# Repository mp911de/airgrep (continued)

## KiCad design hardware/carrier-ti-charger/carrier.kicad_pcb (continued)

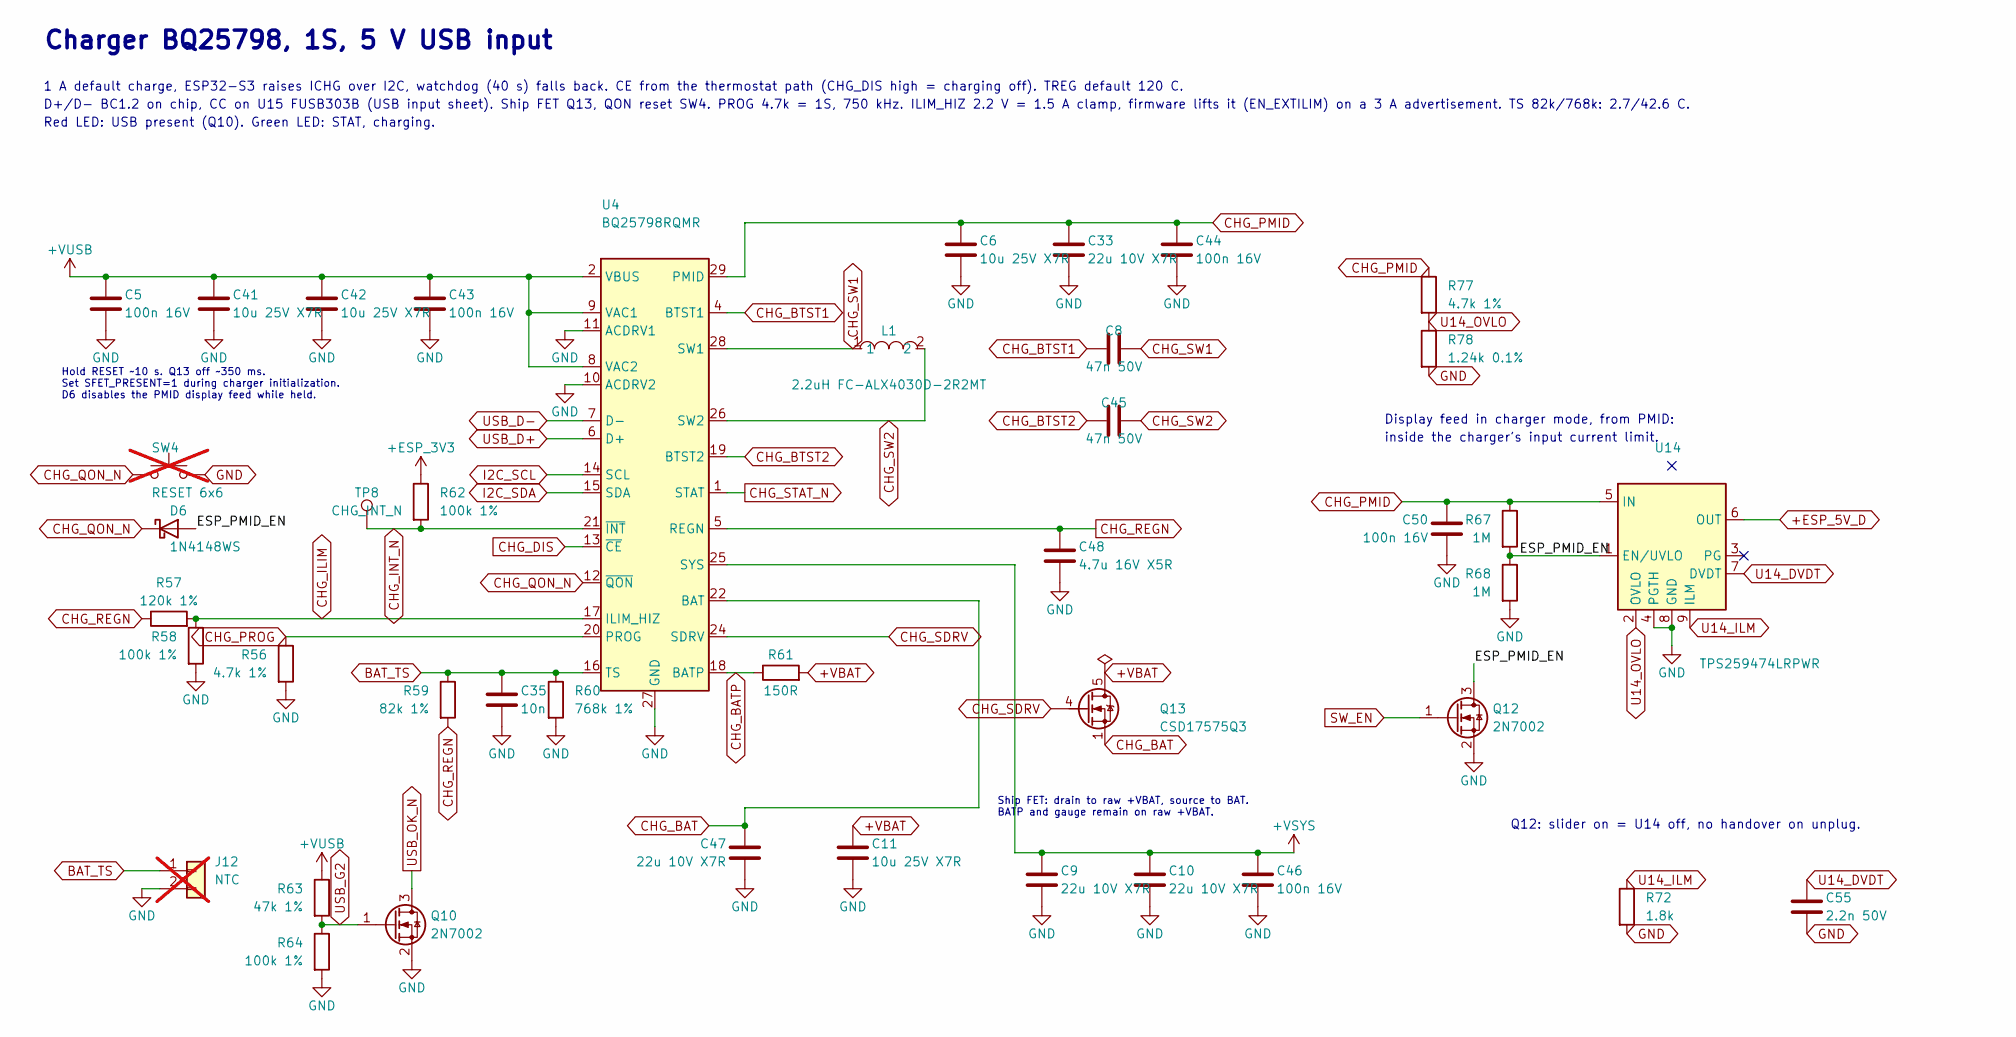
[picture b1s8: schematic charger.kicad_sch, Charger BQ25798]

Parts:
C5, C43, C44, C46, C50: 100n 16V; C_0402_1005Metric_NoSilk; MPN CL05B104KO5NNNC; LCSC C1525
C6, C11, C41, C42: 10u 25V X7R; C_0805_2012Metric; LCSC C3039694
C8, C45: 47n 50V; C_0603_1608Metric; LCSC C1622
C9, C10, C33, C47: 22u 10V X7R; C_0805_2012Metric; LCSC C907991
C35: 10n; C_0603_1608Metric; LCSC C57112
C48: 4.7u 16V X5R; C_0603_1608Metric; LCSC C19666
C55: 2.2n 50V; C_0603_1608Metric; MPN 0603B222K500NT; LCSC C1604
D6: 1N4148WS; D_SOD-323; MPN 1N4148WS; LCSC C2128
J12: NTC; JST_PH_B2B-PH-K_1x02_P2.00mm_Vertical_R10; not fitted
L1: 2.2uH FC-ALX4030D-2R2MT; IND-SMD_L4.2-W4.2_FC-ALX4030D; LCSC C5370906
Q10, Q12: 2N7002; SOT-23; LCSC C8545
Q13: CSD17575Q3; VSON-8_3.3x3.3mm_CSD17575Q3; LCSC C529277
R56: 4.7k 1%; R_0402_1005Metric_NoSilk; MPN 0402WGF4701TCE; LCSC C25900
R57: 120k 1%; R_0603_1608Metric; LCSC C25808
R58, R62, R64: 100k 1%; R_0603_1608Metric; LCSC C25803
R59: 82k 1%; R_0603_1608Metric; Tolerance 1%; MPN 0603WAF8202T5E; LCSC C23254
R60: 768k 1%; R_0402_1005Metric_NoSilk; MPN FRC0402F7683TS; LCSC C49196905
R61: 150R; R_0603_1608Metric; LCSC C22808
R63: 47k 1%; R_0603_1608Metric; LCSC C25819
R67, R68: 1M; R_0603_1608Metric; LCSC C22935
R72: 1.8k; R_0603_1608Metric; Tolerance 1%; MPN 0603WAF1801T5E; LCSC C4177
R77: 4.7k 1%; R_0402_1005Metric_NoSilk; Tolerance 1%; MPN 0402WGF4701TCE; LCSC C25900
R78: 1.24k 0.1%; R_0402_1005Metric_NoSilk; Tolerance 0.1%; MPN ARG02BTC1241; LCSC C2984409
SW4: RESET 6x6; SW_PUSH_6mm; not fitted
TP8: CHG_INT_N; TestPoint_Pad_D1.5mm
U4: BQ25798RQMR; Texas_RQM0029A_VQFN-29_4x4mm_P0.4mm; LCSC C2876593
U14: TPS259474LRPWR; VQFN-10_L2.0-W2.0-P0.45-HR_LM73100; LCSC C2864845

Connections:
+ESP_3V3: R62.1; also elsewhere on the board
+ESP_5V_D: U14.6 (OUT); also elsewhere on the board
+VBAT: C11.1, Q13.5 (D), R61.2; also elsewhere on the board
+VSYS: C9.1, C10.1, C46.1, U4.25 (SYS); also elsewhere on the board
+VUSB: C5.1, C41.1, C42.1, C43.1, R63.1, U4.2 (VBUS), U4.3 (VBUS), U4.8 (VAC2), U4.9 (VAC1); also elsewhere on the board
/Charger BQ25798/ESP_PMID_EN: D6.2 (A), Q12.3 (D), R67.2, R68.1, U14.1 (EN/UVLO)
BAT_TS: C35.1, J12.1, R59.1, R60.1, U4.16 (TS)
CHG_BAT: C47.1, Q13.1 (S), Q13.2 (S), Q13.3 (S), U4.22 (BAT), U4.23 (BAT)
CHG_BATP: R61.1, U4.18 (BATP)
CHG_BTST1: C8.1, U4.4 (BTST1)
CHG_BTST2: C45.1, U4.19 (BTST2)
CHG_DIS: U4.13 (~CE); also elsewhere on the board
CHG_ILIM: R57.2, R58.1, U4.17 (ILIM_HIZ)
CHG_INT_N: R62.2, TP8.1 (1_1), U4.21 (~INT)
CHG_PMID: C6.1, C33.1, C44.1, C50.1, R67.1, R77.1, U4.29 (PMID), U14.5 (IN)
CHG_PROG: R56.1, U4.20 (PROG)
CHG_QON_N: D6.1 (K), SW4.1, U4.12 (~QON)
CHG_REGN: C48.1, R57.1, R59.2, U4.5 (REGN)
CHG_SDRV: Q13.4 (G), U4.24 (SDRV)
CHG_STAT_N: U4.1 (STAT); also elsewhere on the board
CHG_SW1: C8.2, L1.1, U4.28 (SW1)
CHG_SW2: C45.2, L1.2, U4.26 (SW2)
GND: C5.2, C6.2, C9.2, C10.2, C11.2, C33.2, C35.2, C41.2, C42.2, C43.2, C44.2, C46.2, C47.2, C48.2, C50.2, C55.2, J12.2, Q10.2 (S), Q12.2 (S), R56.2, R58.2, R60.2, R64.2, R68.2, R72.2, R78.2, SW4.2, U4.10 (ACDRV2), U4.11 (ACDRV1), U4.27 (GND), U14.4 (PGTH), U14.8 (GND); also elsewhere on the board
I2C_SCL: U4.14 (SCL); also elsewhere on the board
I2C_SDA: U4.15 (SDA); also elsewhere on the board
SW_EN: Q12.1 (G); also elsewhere on the board
U14_DVDT: C55.1, U14.7 (DVDT)
U14_ILM: R72.1, U14.9 (ILM)
U14_OVLO: R77.2, R78.1, U14.2 (OVLO)
USB_D+: U4.6 (D+); also elsewhere on the board
USB_D-: U4.7 (D-); also elsewhere on the board
USB_G2: Q10.1 (G), R63.2, R64.1
USB_OK_N: Q10.3 (D); also elsewhere on the board

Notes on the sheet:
Hold RESET ~10 s. Q13 off ~350 ms. Set SFET_PRESENT=1 during charger initialization. D6 disables the PMID display feed while held.
Ship FET: drain to raw +VBAT, source to BAT. BATP and gauge remain on raw +VBAT.
Display feed in charger mode, from PMID:
1 A default charge, ESP32-S3 raises ICHG over I2C, watchdog (40 s) falls back. CE from the thermostat path (CHG_DIS high = charging off). TREG default 120 C.
inside the charger's input current limit.
Charger BQ25798, 1S, 5 V USB input
D+/D- BC1.2 on chip, CC on U15 FUSB303B (USB input sheet). Ship FET Q13, QON reset SW4. PROG 4.7k = 1S, 750 kHz. ILIM_HIZ 2.2 V = 1.5 A clamp, firmware lifts it (EN_EXTILIM) on a 3 A advertisement. TS 82k/768k: 2.7/42.6 C.
Q12: slider on = U14 off, no handover on unplug.
Red LED: USB present (Q10). Green LED: STAT, charging.

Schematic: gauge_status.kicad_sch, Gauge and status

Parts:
C27: 100n 16V; C_0402_1005Metric_NoSilk; MPN CL05B104KO5NNNC; LCSC C1525
D2: L-115WEGW red/green CC; LED_D3.0mm-3; not fitted
D3: LED 3mm green; LED_D3.0mm; not fitted
Q3, Q4: AO3401A; SOT-23; LCSC C15127
R19, R20: 1.5k; R_0603_1608Metric; Tolerance 1%; MPN 0603WAF1501T5E; LCSC C22843
R23, R26, R31: 470R; R_0603_1608Metric; LCSC C23179
R33: 47k 1%; R_0603_1608Metric; LCSC C25819
R36: 100k 1%; R_0603_1608Metric; LCSC C25803
R90, R91: 5.1k; R_0805_2012Metric_Pad1.20x1.40mm_HandSolder; not fitted
U8: MAX17048G+T10; TDFN-8_L2.0-W2.0-P0.50-EP0.8x1.38_T822; LCSC C2682616

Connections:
+5V: R26.1; also elsewhere on the board
+ESP_3V3: R19.1, R20.1, R90.1, R91.1; also elsewhere on the board
+VBAT: C27.1, U8.2 (CELL), U8.3 (VDD); also elsewhere on the board
+VSYS: Q3.2 (S), Q4.2 (S), R33.1, R36.1; also elsewhere on the board
CHG_STAT_N: Q3.1 (G), R33.2; also elsewhere on the board
GND: C27.2, D2.2 (K), D3.1 (K), U8.1 (CTG), U8.4 (GND), U8.6 (QSTRT), U8.9 (EP); also elsewhere on the board
I2C_SCL: R20.2, R91.2, U8.7 (SCL); also elsewhere on the board
I2C_SDA: R19.2, R90.2, U8.8 (SDA); also elsewhere on the board
LED_CHG_A: D2.1 (A1), R23.2
LED_FULL_A: D2.3 (A2), R31.2
LED_G_A: D3.2 (A), R26.2
LED_G_SW: Q3.3 (D), R31.1
LED_R_SW: Q4.3 (D), R23.1
USB_OK_N: Q4.1 (G), R36.2; also elsewhere on the board

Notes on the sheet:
Fuel gauge
Status LEDs
Fuel gauge (MAX17048) and status LEDs

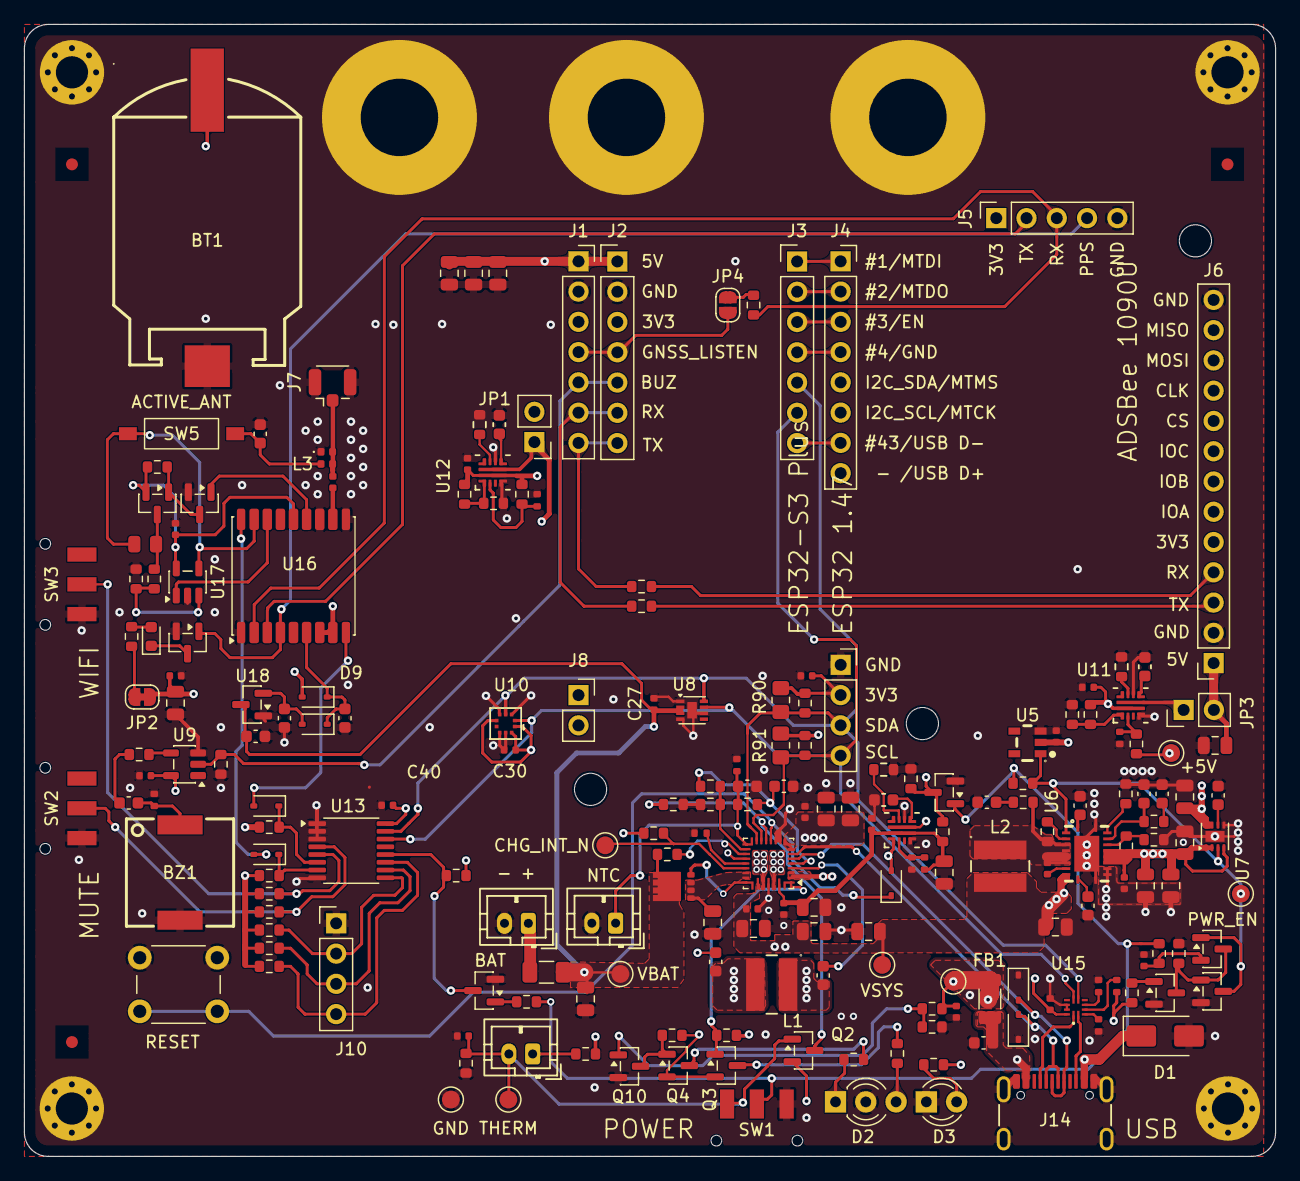
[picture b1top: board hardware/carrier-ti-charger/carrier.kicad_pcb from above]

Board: 4 copper layers, 105.0 x 95.0 mm, 219 parts (0 on the bottom side), 121 nets.

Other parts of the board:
FID1, FID2, FID3: Fiducial; Fiducial_1mm_Mask2mm
MH1, MH2, MH3, MH4: MountingHole_2.7mm_M2.5_Pad_Via
MH6ANTGNSS, MH7ADS1090, MH8ADS980: MountingHole_6.5mm_Pad
MH12, MH13, MH14: MountingHole_2.7mm_M2.5

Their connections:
GND: MH1.1, MH2.1, MH3.1, MH4.1, MH6ANTGNSS.1, MH7ADS1090.1, MH8ADS980.1; also elsewhere on the board

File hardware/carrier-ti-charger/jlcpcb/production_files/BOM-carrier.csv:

Comment,Designator,Footprint,LCSC,Quantity
1.24k 0.1%,R78,R_0402_1005Metric_NoSilk,C2984409,1
1.5k,"R19,R20",R_0603_1608Metric,C22843,2
1.5k 1%,"R74,R76,R79",R_0402_1005Metric_NoSilk,C25867,3
1.8k,"R70,R71,R72",R_0603_1608Metric,C4177,3
10 Ω 1% 0805,R82,R_0805_2012Metric_NoSilk,C17415,1
100k 1%,"R12,R13,R27,R36,R41,R48,R49,R52,R53,R54,R55,R58,R62,R64,R69,R83,R85,R88,R89",R_0603_1608Metric,C25803,19
100n 16V,"C12,C16,C27,C28,C29,C30,C31,C37,C38,C39,C40,C43,C44,C46,C5,C50,C53,C57,C60,C61",C_0402_1005Metric_NoSilk,C1525,20
100p,C22,C_0603_1608Metric,C14858,1
10k,R87,R_0402_1005Metric_NoSilk,C25744,1
10k,R40,R_0603_1608Metric,C25804,1
10n,"C21,C23,C35,C59",C_0603_1608Metric,C57112,4
10u 25V X7R,"C11,C24,C25,C26,C41,C42,C6,C62",C_0805_2012Metric,C3039694,8
120k 1%,R57,R_0603_1608Metric,C25808,1
150R,"R61,R86",R_0603_1608Metric,C22808,2
160k,R17,R_0603_1608Metric,C22813,1
1M,"R10,R42,R44,R45,R46,R47,R67,R68",R_0603_1608Metric,C22935,8
1N4148WS,"D11,D12,D6,D8,D9",D_SOD-323,C2128,5
1k,"R28,R29,R30,R32,R43",R_0603_1608Metric,C21190,5
1u,"C63,C64,C65,C66",C_0603_1608Metric,C15849,4
2.2n 50V,"C54,C55,C56",C_0603_1608Metric,C1604,3
2.2uH FC-ALX4030D-2R2MT,"L1,L2",IND-SMD_L4.2-W4.2_FC-ALX4030D,C5370906,2
220k,R16,R_0603_1608Metric,C22961,1
22u 10V X7R,"C10,C13,C14,C18,C19,C20,C33,C47,C51,C52,C9",C_0805_2012Metric,C907991,11
240k 1%,R14,R_0603_1608Metric,C4197,1
27nH,L3,L_0402_1005Metric,C12669,1
2N7002,"Q10,Q11,Q12,Q15,Q16,Q8,Q9",SOT-23,C8545,7
4.7k 1%,"R56,R77",R_0402_1005Metric_NoSilk,C25900,2
4.7u 16V X5R,"C1,C15,C48",C_0603_1608Metric,C19666,3
470R,"R23,R26,R31",R_0603_1608Metric,C23179,3
47k 1%,"R33,R63",R_0603_1608Metric,C25819,2
47n 50V,"C17,C45,C8",C_0603_1608Metric,C1622,3
47p C0G,C58,C_0402_1005Metric_NoSilk,C1567,1
5.6k 1%,"R73,R75",R_0603_1608Metric,C23189,2
560R,R84,R_0603_1608Metric,C23204,1
5A 0466005.NRHF,F1,Fuse_1206_3216Metric,C57525,1
6.8k,R18,R_0603_1608Metric,C23212,1
75k 1%,R15,R_0603_1608Metric,C23242,1
768k 1%,"R60,R80,R81",R_0402_1005Metric_NoSilk,C49196905,3
82k 1%,R59,R_0603_1608Metric,C23254,1
ACTIVE_ANT,SW5,SW-SMD_SHOUHAN_2.54-1P_TPGT,C7421519,1
AO3401A,"Q14,Q2,Q3,Q4,Q7",SOT-23,C15127,5
BLM31KN471SZ1L,FB1,L_1206_3216Metric,C710518,1
BMP580,U10,LGA-10_L2.0-W2.0-P0.50-TL_BMP581,C22391138,1
BQ25798RQMR,U4,Texas_RQM0029A_VQFN-29_4x4mm_P0.4mm,C2876593,1
CR2032,BT1,BAT-SMD_BS-CR2032-8,C7498149,1
CSD17575Q3,Q13,VSON-8_3.3x3.3mm_CSD17575Q3,C529277,1
FUSB303BTMX,U15,X2QFN-12_L1.6-W1.6-P0.40-TL,C895444,1
GNSS_ANT,J7,U.FL_Hirose_U.FL-R-SMT-1_Vertical,C88374,1
H5VLD3B ESD 5V,"D4,D5",D_SOD-323,C20615805,2
K3-1280S-F1,"SW1,SW2,SW3",SW-SMD_K3-1280S-F1,C92658,3
KT-0603W white,D10,LED_0603_1608Metric,C2290,1
MAX-M10S-00B,U16,ublox_MAX-M10S,C4153167,1
MAX17048G+T10,U8,TDFN-8_L2.0-W2.0-P0.50-EP0.8x1.38_T822,C2682616,1
MC-107DMS,J14,USB_C_Receptacle_Hanbo_MC-107DMS,C3039295,1
PESD0402-140,D7,D_0402_1005Metric,C10662,1
PKMCS0909E4000-R1,BZ1,BUZ-SMD_L9.0-W9.0_PKMCS0909E4000-R1,C910763,1
SMAJ12A,D1,D_SMA,C19077531,1
SN74LVC1G17DBVR,U9,SOT-23-5,C7836,1
TCA9534PWR,U13,TSSOP-16_4.4x5mm_P0.65mm,C783615,1
TLV840CADL29DBVR 2.9V,U5,SOT-23-5_L2.9-W1.6-P0.95-LS2.8-BR,C3686404,1
TLV9001IDBVR,U17,SOT-23-5,C398363,1
TPS22975DSGR,U7,Texas_DSG0008A_WSON-8-1EP_2x2mm_P0.5mm_EP0.9x1.6mm,C524777,1
TPS259474LRPWR,"U11,U12,U14",VQFN-10_L2.0-W2.0-P0.45-HR_LM73100,C2864845,3
TPS61088RHLR,U6,VQFN-20_L4.6-W3.6-P0.50-BL,C87357,1
XC6206P332MR,U18,SOT-23,C5446,1

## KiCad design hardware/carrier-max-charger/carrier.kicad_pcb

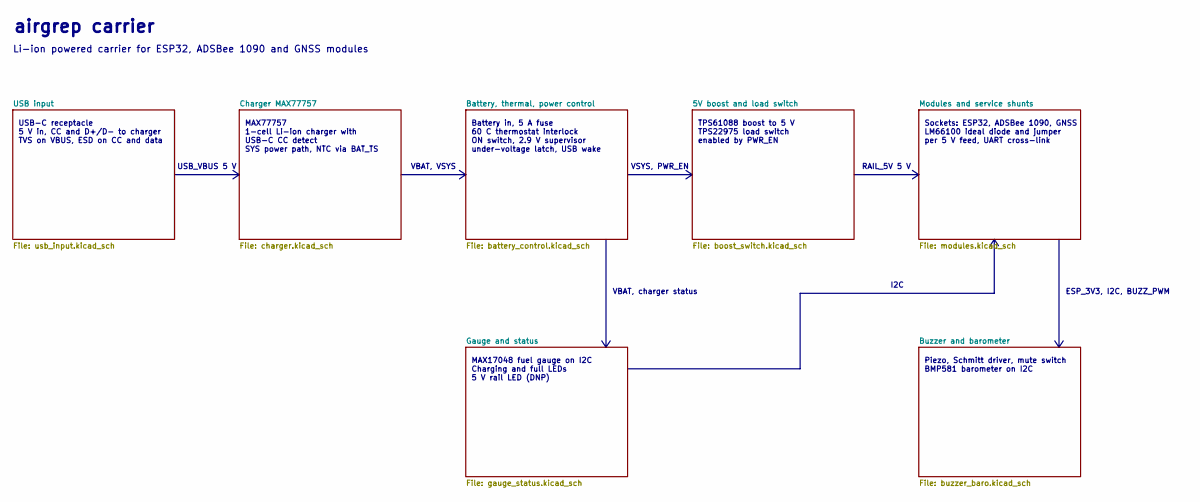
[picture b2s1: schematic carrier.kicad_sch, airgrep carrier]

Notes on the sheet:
I2C
TPS61088 boost to 5 V TPS22975 load switch enabled by PWR_EN
Piezo, Schmitt driver, mute switch BMP581 barometer on I2C
MAX77757 1-cell Li-ion charger with USB-C CC detect SYS power path, NTC via BAT_TS
airgrep carrier
VBAT, VSYS
ESP_3V3, I2C, BUZZ_PWM
VBAT, charger status
Sockets: ESP32, ADSBee 1090, GNSS LM66100 ideal diode and jumper per 5 V feed, UART cross-link
Battery in, 5 A fuse 60 C thermostat interlock ON switch, 2.9 V supervisor under-voltage latch, USB wake
USB_VBUS 5 V
RAIL_5V 5 V
USB-C receptacle 5 V in, CC and D+/D- to charger TVS on VBUS, ESD on CC and data
MAX17048 fuel gauge on I2C Charging and full LEDs 5 V rail LED (DNP)
VSYS, PWR_EN
Li-ion powered carrier for ESP32, ADSBee 1090 and GNSS modules

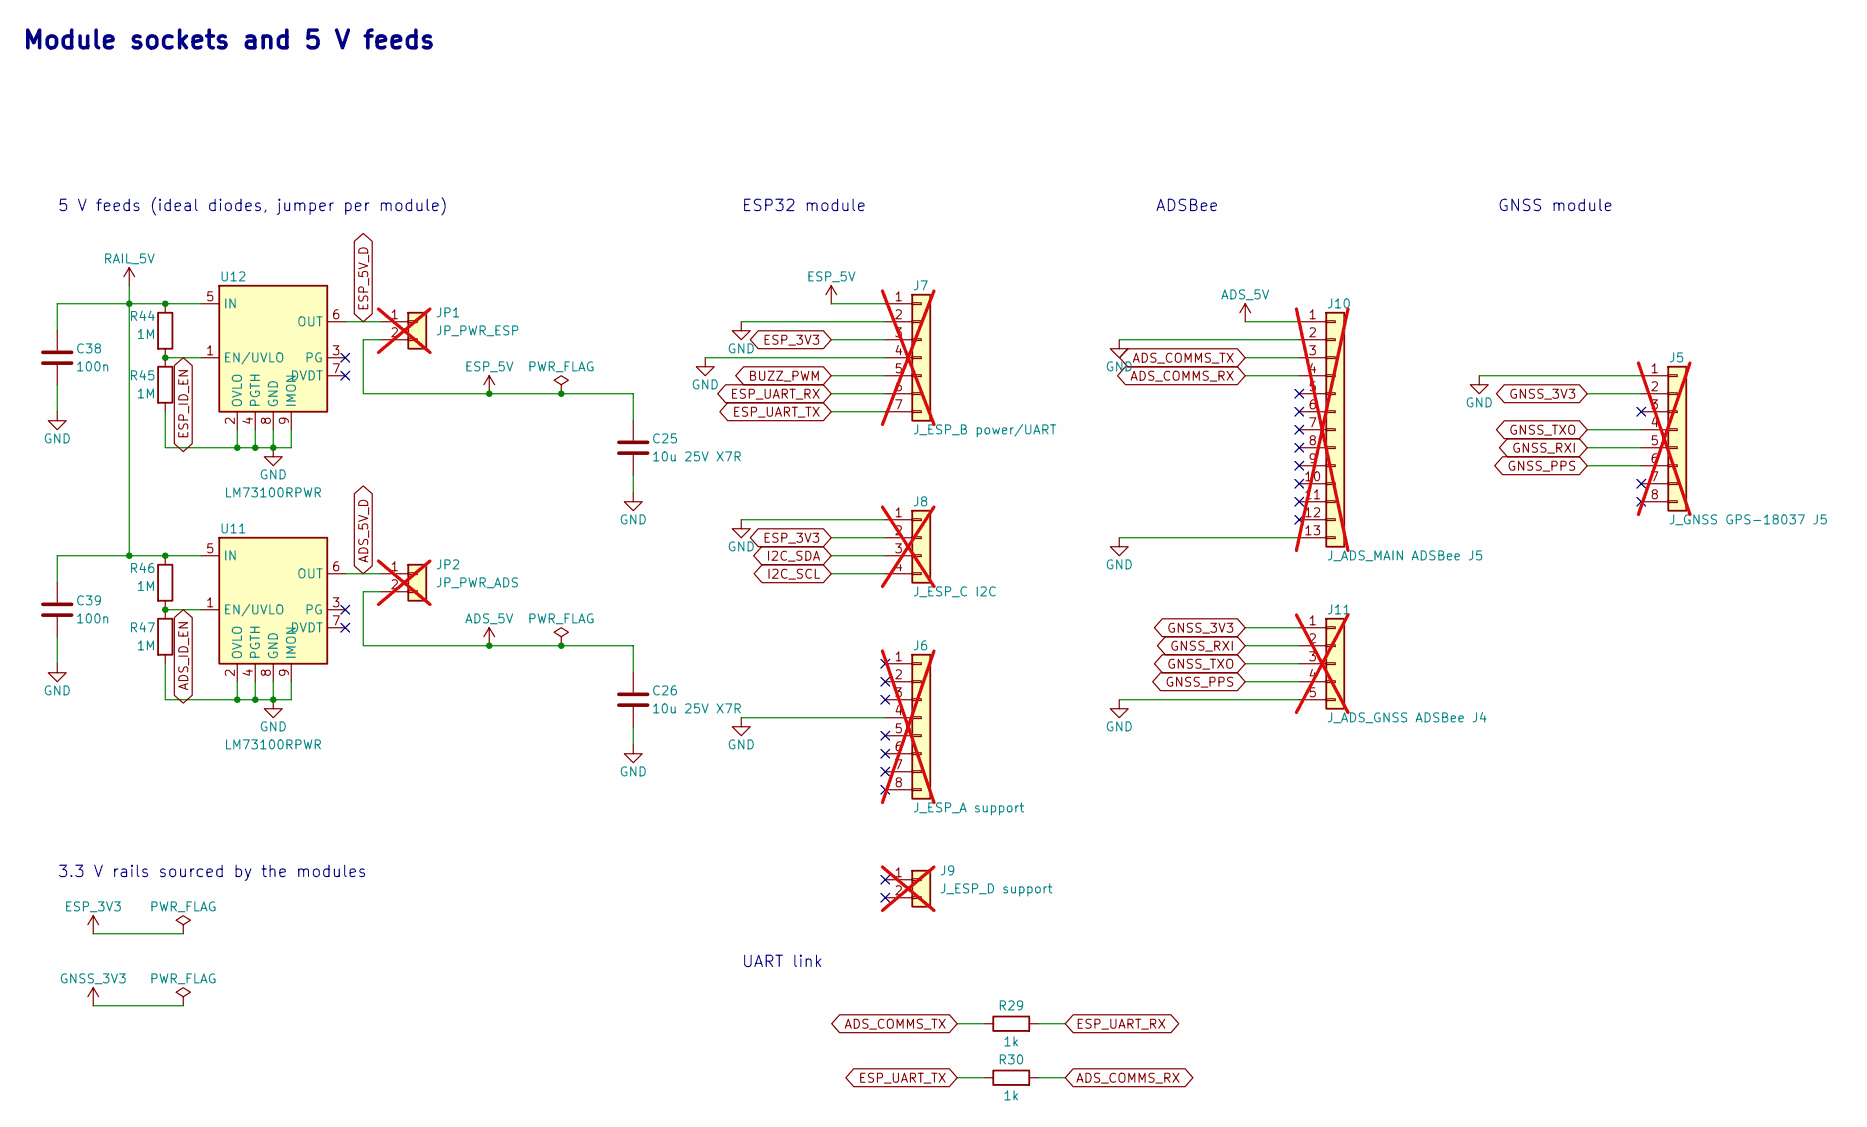
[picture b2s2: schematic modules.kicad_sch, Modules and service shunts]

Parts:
C25, C26: 10u 25V X7R; C_0805_2012Metric; LCSC C3039694
C38, C39: 100n; C_0603_1608Metric; LCSC C14663
J5: J_GNSS GPS-18037 J5; PinSocket_1x08_P2.54mm_Vertical; not fitted
J6: J_ESP_A support; PinSocket_1x08_P2.54mm_Vertical; not fitted
J7: J_ESP_B power/UART; PinSocket_1x07_P2.54mm_Vertical; not fitted
J8: J_ESP_C I2C; PinSocket_1x04_P2.54mm_Vertical; not fitted
J9: J_ESP_D support; PinSocket_1x02_P2.54mm_Vertical; not fitted
J10: J_ADS_MAIN ADSBee J5; PinSocket_1x13_P2.54mm_Vertical; not fitted
J11: J_ADS_GNSS ADSBee J4; PinSocket_1x05_P2.54mm_Vertical; not fitted
JP1: JP_PWR_ESP; PinHeader_1x02_P2.54mm_Vertical; not fitted
JP2: JP_PWR_ADS; PinHeader_1x02_P2.54mm_Vertical; not fitted
R29, R30: 1k; R_0603_1608Metric; LCSC C21190
R44, R45, R46, R47: 1M; R_0603_1608Metric; LCSC C22935
U11, U12: LM73100RPWR; VQFN-10_L2.0-W2.0-P0.45-HR_LM73100; LCSC C3210761

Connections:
ADS_5V: C26.1, J10.1, JP2.2
ADS_5V_D: JP2.1, U11.6 (OUT)
ADS_COMMS_RX: J10.4, R30.2
ADS_COMMS_TX: J10.3, R29.1
ADS_ID_EN: R46.2, R47.1, U11.1 (EN/UVLO)
BUZZ_PWM: J7.5; also elsewhere on the board
ESP_3V3: J7.3, J8.2; also elsewhere on the board
ESP_5V: C25.1, J7.1, JP1.2
ESP_5V_D: JP1.1, U12.6 (OUT)
ESP_ID_EN: R44.2, R45.1, U12.1 (EN/UVLO)
ESP_UART_RX: J7.6, R29.2
ESP_UART_TX: J7.7, R30.1
GND: C25.2, C26.2, C38.2, C39.2, J5.1, J6.4 (Pin_4_4), J7.2, J7.4, J8.1, J10.2, J10.13, J11.5, R45.2, R47.2, U11.2 (OVLO), U11.4 (PGTH), U11.8 (GND), U11.9 (IMON), U12.2 (OVLO), U12.4 (PGTH), U12.8 (GND), U12.9 (IMON); also elsewhere on the board
GNSS_3V3: J5.2, J11.1
GNSS_PPS: J5.6, J11.4
GNSS_RXI: J5.5, J11.2
GNSS_TXO: J5.4, J11.3
I2C_SCL: J8.4; also elsewhere on the board
I2C_SDA: J8.3; also elsewhere on the board
RAIL_5V: C38.1, C39.1, R44.1, R46.1, U11.5 (IN), U12.5 (IN); also elsewhere on the board

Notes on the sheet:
Module sockets and 5 V feeds
UART link
ADSBee
GNSS module
3.3 V rails sourced by the modules
5 V feeds (ideal diodes, jumper per module)
ESP32 module

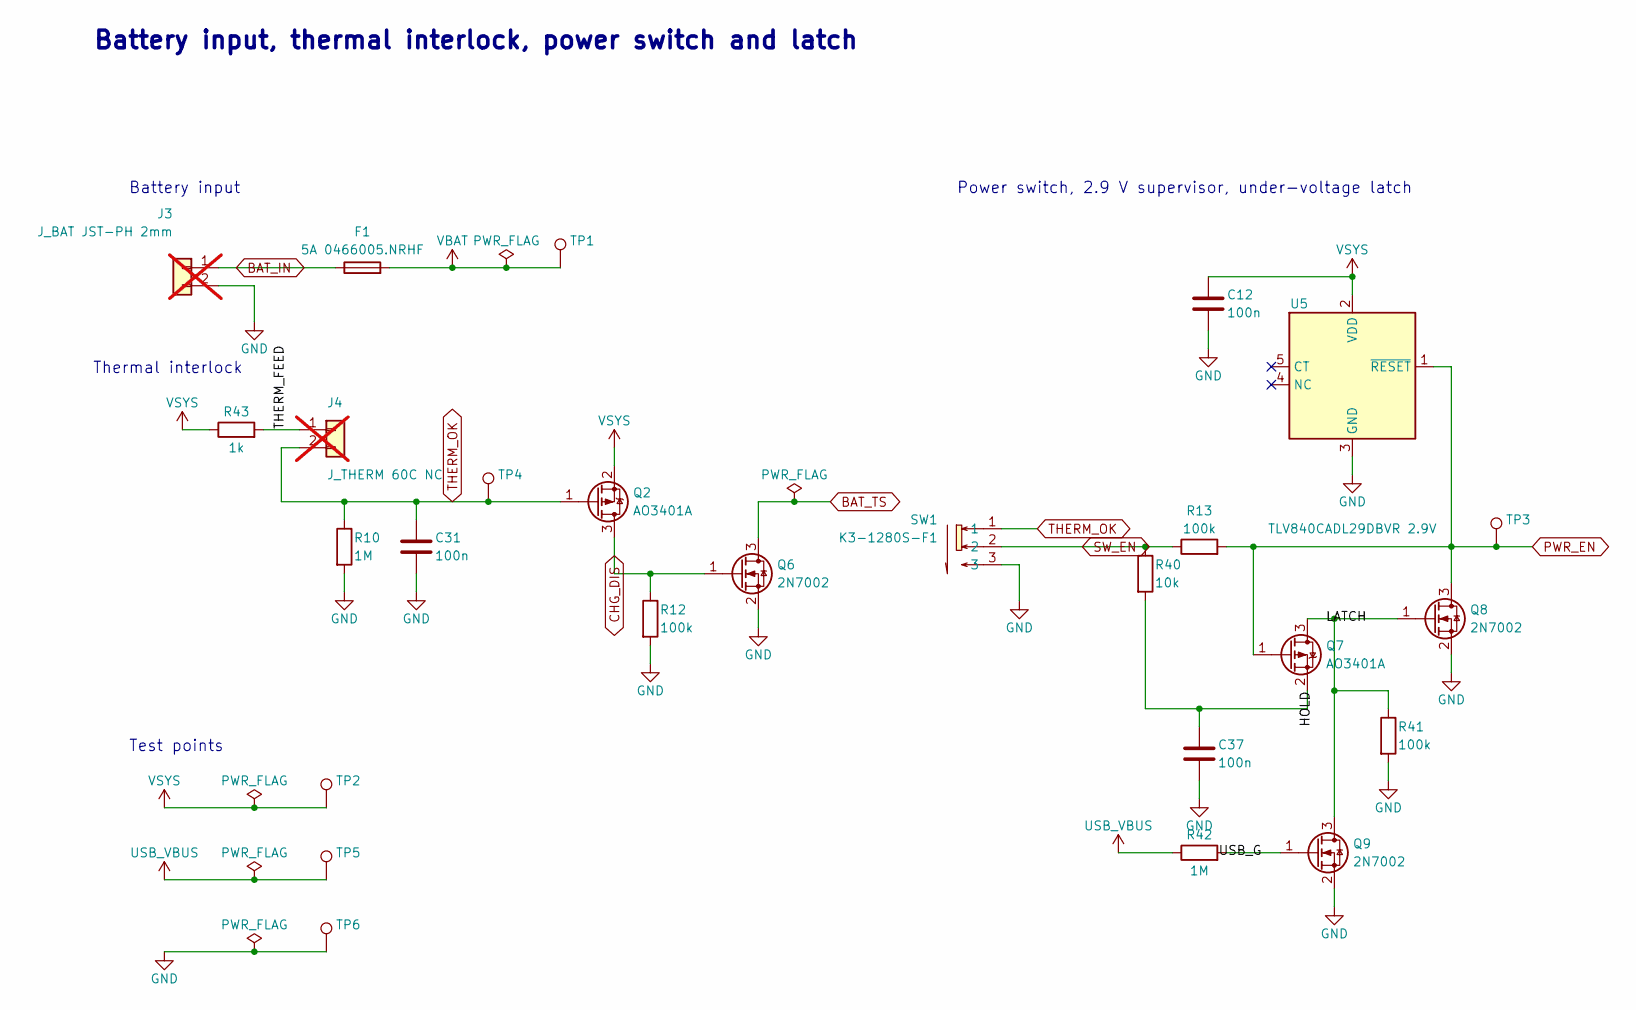
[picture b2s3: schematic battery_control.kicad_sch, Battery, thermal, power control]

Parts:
C12, C31, C37: 100n; C_0603_1608Metric; LCSC C14663
F1: 5A 0466005.NRHF; Fuse_1206_3216Metric; LCSC C57525
J3: J_BAT JST-PH 2mm; JST_PH_B2B-PH-K_1x02_P2.00mm_Vertical_R10; not fitted
J4: J_THERM 60C NC; JST_PH_B2B-PH-K_1x02_P2.00mm_Vertical_R10; not fitted
Q2, Q7: AO3401A; SOT-23; LCSC C15127
Q6, Q8, Q9: 2N7002; SOT-23; LCSC C8545
R10, R42: 1M; R_0603_1608Metric; LCSC C22935
R12, R13, R41: 100k; R_0603_1608Metric; LCSC C25803
R40: 10k; R_0603_1608Metric; LCSC C25804
R43: 1k; R_0603_1608Metric; LCSC C21190
SW1: K3-1280S-F1; SW-SMD_K3-1280S-F1; LCSC C92658
TP1: VBAT; TestPoint_Pad_D1.5mm
TP2: VSYS; TestPoint_Pad_D1.5mm
TP3: PWR_EN; TestPoint_Pad_D1.5mm
TP4: THERM_OK; TestPoint_Pad_D1.5mm
TP5: USB_VBUS; TestPoint_Pad_D1.5mm
TP6: GND; TestPoint_Pad_D1.5mm
U5: TLV840CADL29DBVR 2.9V; SOT-23-5_L2.9-W1.6-P0.95-LS2.8-BR; LCSC C3686404

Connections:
/Battery, thermal, power control/HOLD: C37.2, Q7.2 (S), R40.2
/Battery, thermal, power control/LATCH: Q7.3 (D), Q8.1 (G), Q9.3 (D), R41.1
/Battery, thermal, power control/THERM_FEED: J4.1, R43.2
/Battery, thermal, power control/USB_G: Q9.1 (G), R42.2
BAT_IN: F1.1, J3.1
BAT_TS: Q6.3 (D); also elsewhere on the board
CHG_DIS: Q2.3 (D), Q6.1 (G), R12.1
GND: C12.2, C31.2, C37.1, J3.2, Q6.2 (S), Q8.2 (S), Q9.2 (S), R10.2, R12.2, R41.2, SW1.3, TP6.1 (1_1), U5.3 (GND); also elsewhere on the board
PWR_EN: Q7.1 (G), Q8.3 (D), R13.2, TP3.1 (1_1), U5.1 (~RESET); also elsewhere on the board
SW_EN: R13.1, R40.1, SW1.2
THERM_OK: C31.1, J4.2, Q2.1 (G), R10.1, SW1.1, TP4.1 (1_1)
USB_VBUS: R42.1, TP5.1 (1_1); also elsewhere on the board
VBAT: F1.2, TP1.1 (1_1); also elsewhere on the board
VSYS: C12.1, Q2.2 (S), R43.1, TP2.1 (1_1), U5.2 (VDD); also elsewhere on the board

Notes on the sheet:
Battery input
Battery input, thermal interlock, power switch and latch
Power switch, 2.9 V supervisor, under-voltage latch
Test points
Thermal interlock

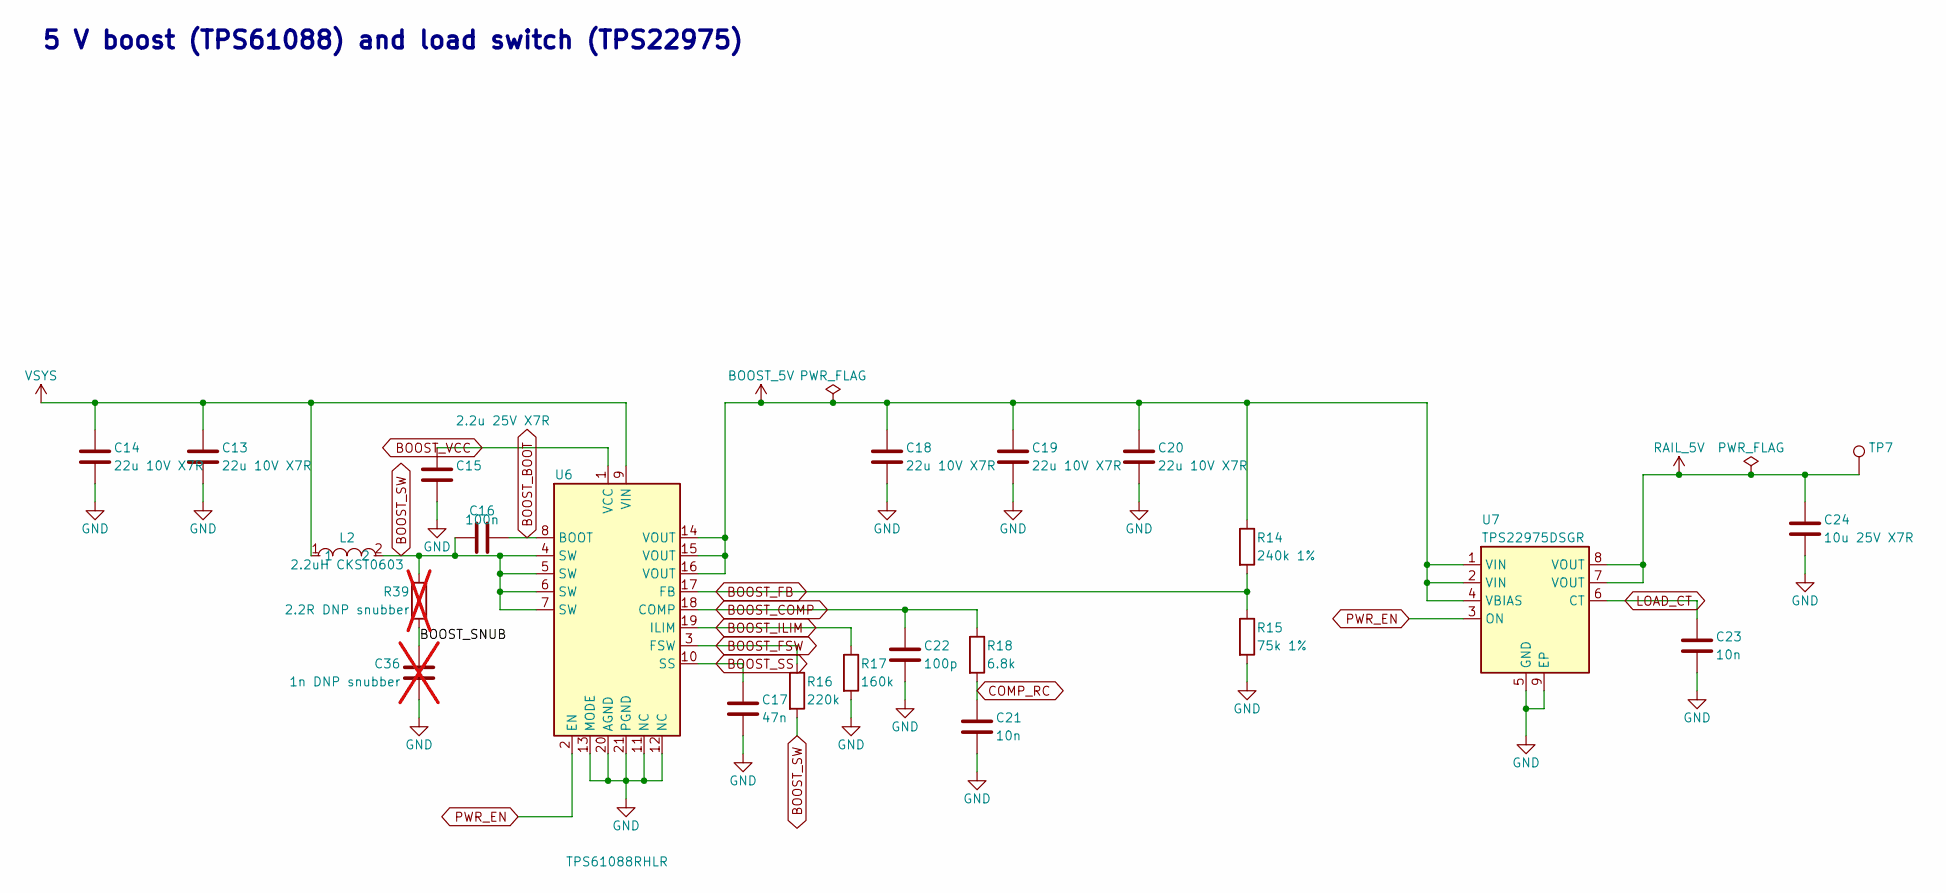
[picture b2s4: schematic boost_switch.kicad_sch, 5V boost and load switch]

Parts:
C13, C14, C18, C19, C20: 22u 10V X7R; C_0805_2012Metric; LCSC C907991
C15: 2.2u 25V X7R; C_0603_1608Metric; LCSC C415535
C16: 100n; C_0603_1608Metric; LCSC C14663
C17: 47n; C_0603_1608Metric; LCSC C1622
C21, C23: 10n; C_0603_1608Metric; LCSC C57112
C22: 100p; C_0603_1608Metric; LCSC C14858
C24: 10u 25V X7R; C_0805_2012Metric; LCSC C3039694
C36: 1n DNP snubber; C_0603_1608Metric; not fitted
L2: 2.2uH CKST0603; IND-SMD_L7.4-W6.6; LCSC C3002634
R14: 240k 1%; R_0603_1608Metric; LCSC C4197
R15: 75k 1%; R_0603_1608Metric; LCSC C23242
R16: 220k; R_0603_1608Metric; LCSC C22961
R17: 160k; R_0603_1608Metric; LCSC C22813
R18: 6.8k; R_0603_1608Metric; LCSC C23212
R39: 2.2R DNP snubber; R_0603_1608Metric; not fitted
TP7: RAIL_5V; TestPoint_Pad_D1.5mm
U6: TPS61088RHLR; VQFN-20_L4.6-W3.6-P0.50-BL; LCSC C87357
U7: TPS22975DSGR; Texas_DSG0008A_WSON-8-1EP_2x2mm_P0.5mm_EP0.9x1.6mm; LCSC C524777

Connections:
/5V boost and load switch/BOOST_SNUB: C36.1, R39.2
BOOST_5V: C18.1, C19.1, C20.1, R14.1, U6.14 (VOUT), U6.15 (VOUT), U6.16 (VOUT), U7.1 (VIN), U7.2 (VIN), U7.4 (VBIAS)
BOOST_BOOT: C16.1, U6.8 (BOOT)
BOOST_COMP: C22.1, R18.1, U6.18 (COMP)
BOOST_FB: R14.2, R15.1, U6.17 (FB)
BOOST_FSW: R16.1, U6.3 (FSW)
BOOST_ILIM: R17.1, U6.19 (ILIM)
BOOST_SS: C17.1, U6.10 (SS)
BOOST_SW: C16.2, L2.2, R16.2, R39.1, U6.4 (SW), U6.5 (SW), U6.6 (SW), U6.7 (SW)
BOOST_VCC: C15.1, U6.1 (VCC)
COMP_RC: C21.1, R18.2
GND: C13.2, C14.2, C15.2, C17.2, C18.2, C19.2, C20.2, C21.2, C22.2, C23.2, C24.2, C36.2, R15.2, R17.2, U6.11 (NC), U6.12 (NC), U6.13 (MODE), U6.20 (AGND), U6.21 (PGND), U7.5 (GND), U7.9 (EP); also elsewhere on the board
LOAD_CT: C23.1, U7.6 (CT)
PWR_EN: U6.2 (EN), U7.3 (ON); also elsewhere on the board
RAIL_5V: C24.1, TP7.1 (1_1), U7.7 (VOUT), U7.8 (VOUT); also elsewhere on the board
VSYS: C13.1, C14.1, L2.1, U6.9 (VIN); also elsewhere on the board

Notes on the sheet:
5 V boost (TPS61088) and load switch (TPS22975)
